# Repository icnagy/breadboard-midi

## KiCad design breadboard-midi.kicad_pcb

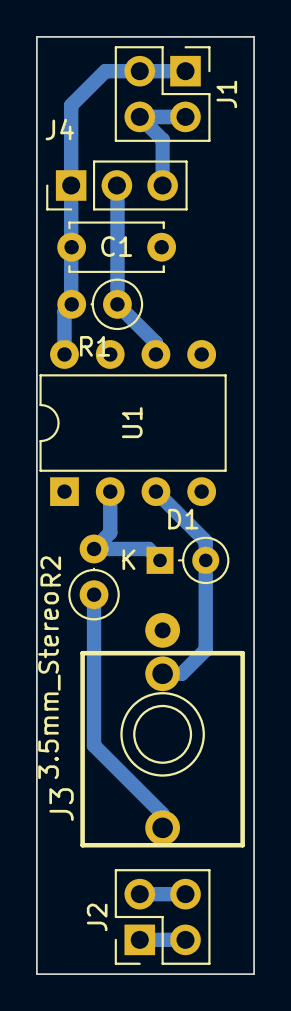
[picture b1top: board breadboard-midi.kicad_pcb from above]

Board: 2 copper layers, 12.1 x 52.1 mm, 9 parts (0 on the bottom side), 7 nets.

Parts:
C1: 0.1uF; C_Disc_D5.0mm_W2.5mm_P5.00mm
D1: 1n4148; D_DO-34_SOD68_P2.54mm_Vertical_KathodeUp
J1, J2: Conn_02x02_Odd_Even; PinHeader_2x02_P2.54mm_Vertical
J3: 3.5mm_Stereo; EighthInch_PJ398SM
J4: Conn_01x03; PinHeader_1x03_P2.54mm_Vertical
R1, R2: 220; R_Axial_DIN0207_L6.3mm_D2.5mm_P2.54mm_Vertical
U1: 6N137; DIP-8_W7.62mm

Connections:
+5VA: C1.1, J1.1, J1.3, J4.1, R1.2, U1.8 (VCC)
/MIDI_IN: J4.2, R1.1, U1.6 (VO)
GNDA: C1.2, J1.2, J1.4, J2.2, J2.4, J4.3, U1.5 (GND)
unnamed: D1.1 (K), R2.2, U1.2 (A)
unnamed: D1.2 (A), J3.3 (SW), U1.3 (C)
unnamed: J2.1, J2.3
unnamed: J3.1 (SIG), R2.1

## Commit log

2022-04-21 Remove unused files
2022-06-10 Add image and schematic
2022-06-10 Add readme
2023-05-29 Kicad 7.0.5 upgrade
